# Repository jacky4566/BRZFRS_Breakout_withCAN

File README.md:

# BRZFRS_Breakout_withCAN

An inline ECU breakout board for the Subaru BRZ / Scion FR-S / Toyota 86 with a built-in CAN I/O module.

**CURRENTLY UNTESTED**

The board sits between your aftermarket ECU and the vehicle harness. All 135 ECU pins pass straight through. The board also taps the ECU's CAN bus and +5V supply to power a small STM32 module. That module reads extra analog and digital inputs, sends them on the CAN bus, and drives four low-side outputs on CAN command.

## Credits

The CAN I/O section is based on **[CANBoard](https://github.com/corygrant/CANBoard) by Cory Grant**, released under the MIT License (see [LICENSE.MD](LICENSE.MD)). This board adapts that design to the BRZ/FRS ECU connector form factor.

## Firmware

This board **requires Cory Grant's CANBoard firmware**. It does not work without it. Get the firmware, CAN message definitions and setup instructions from the original project:
https://github.com/corygrant/dingoFW

The MCU, CAN transceiver and I/O pin assignments come from the original CANBoard design. Refer to that project for the CAN message format and IDs.

### Programming

Flash the firmware over SWD with the **J1 Tag-Connect TC2030** footprint and an ST-Link (or another SWD probe) with a TC2030 cable.

## ECU connector taps

Every pin from J3 to J2 is wired 1:1. The CAN module connects to only these pins:

| ECU pin | Net | Use |
|--------:|-----|-----|
| A18 (18) | CAN_L | CAN bus low |
| A19 (19) | CAN_H | CAN bus high |
| D19 (120) | +5V | Powers the CAN module and the +5V pins on the headers |
| D29 (130) | GND | Signal ground |
| D03 (104), D04(105) | GNDPWR | Power ground for the output drivers |

The module runs from the ECU's +5V supply, so everything on the board and on the header +5V pins shares that supply. Keep the external load on the +5V pins small.

## Inputs

### Analog inputs: J7 (5 channels)

Each analog input has a 4.7k series resistor, a 10k resistor to ground and a 10nF filter capacitor before the STM32 ADC. The divider scales the input by about 0.68, so 3.3V at the ADC is about 4.85V at the pin.

Each input has a +5V pin next to it, so J7 can connect 3-wire sensors (signal, +5V, ground on J6) directly.

| J7 pin | Signal | MCU pin |
|-------:|--------|---------|
| 1 | +5V | |
| 2 | AI1 | PA0 |
| 3 | +5V | |
| 4 | AI2 | PA1 |
| 5 | +5V | |
| 6 | AI3 | PA2 |
| 7 | +5V | |
| 8 | AI4 | PA3 |
| 9 | +5V | |
| 10 | AI5 | PA4 |

### Digital inputs: J5 (8 channels)

Each digital input has a 10k series resistor to the MCU. There are no external pull-up or pull-down resistors. Input bias comes from the firmware's MCU pin configuration.

| J5 pin | Signal | MCU pin |
|-------:|--------|---------|
| 1 | DI1 | PA5 |
| 2 | DI2 | PA6 |
| 3 | DI3 | PA7 |
| 4 | DI4 | PB0 |
| 5 | DI5 | PB1 |
| 6 | DI6 | PA8 |
| 7 | DI7 | PA9 |
| 8 | DI8 | PA10 |

## Outputs

### Low-side outputs: J4 (4 channels)

The outputs use two NCV8402D dual low-side drivers. Each channel switches its pin to power ground (GNDPWR) and is rated for:

- 42V, 2A per channel
- Short-circuit protection
- Thermal shutdown with automatic restart
- Overvoltage protection
- Built-in clamp for inductive loads (relays, solenoids)

Connect the load between a positive supply and the DIGOUT pin. The supply can be the +5V pin beside each output (small 5V loads only) or switched 12V from the vehicle (relays, lamps, solenoids). The driver completes the circuit to ground when the output is on.

| J4 pin | Signal | MCU pin |
|-------:|--------|---------|
| 1 | DIGOUT1 | PA15 |
| 2 | +5V | |
| 3 | DIGOUT2 | PB3 |
| 4 | +5V | |
| 5 | DIGOUT3 | PB4 |
| 6 | +5V | |
| 7 | DIGOUT4 | PB5 |
| 8 | +5V | |

### Ground: J6

J6 pins 1 to 4 are all signal GND, for sensor and switch returns.

## CAN ID selection

Solder jumpers **JP1** (PB7) and **JP2** (PB6) select the module's CAN ID, as on the original CANBoard. Bridging a jumper (1) pulls its pin high through a 10k resistor.

| JP1 | JP2 | CAN ID |
|:---:|:---:|:------:|
| 0 | 0 | 0x640 |
| 1 | 0 | 0x650 |
| 0 | 1 | 0x660 |
| 1 | 1 | 0x670 |

See the [CANBoard firmware](https://github.com/corygrant/CANBoard) for the message layout at each ID.

## Repository contents

| File / folder | Description |
|---------------|-------------|
| `BRZ_Breakout_withCAN.kicad_pro` | KiCad project |
| `BRZ_Breakout_withCAN.kicad_sch` | Top-level schematic (ECU connectors and I/O headers) |
| `CANBoard.kicad_sch` | CAN module sub-sheet (MCU, CAN, power, I/O conditioning) |
| `BRZ_Breakout_withCAN.kicad_pcb` | PCB layout |
| `6376430-2/`, `Project.pretty/`, `*.kicad_sym` | Project symbols, footprints and 3D model for the ECU connector and NCV8402D |
| `bom/ibom.html` | Interactive BOM |

## License

MIT. See [LICENSE.MD](LICENSE.MD). The original CANBoard design is © 2023 Cory Grant.

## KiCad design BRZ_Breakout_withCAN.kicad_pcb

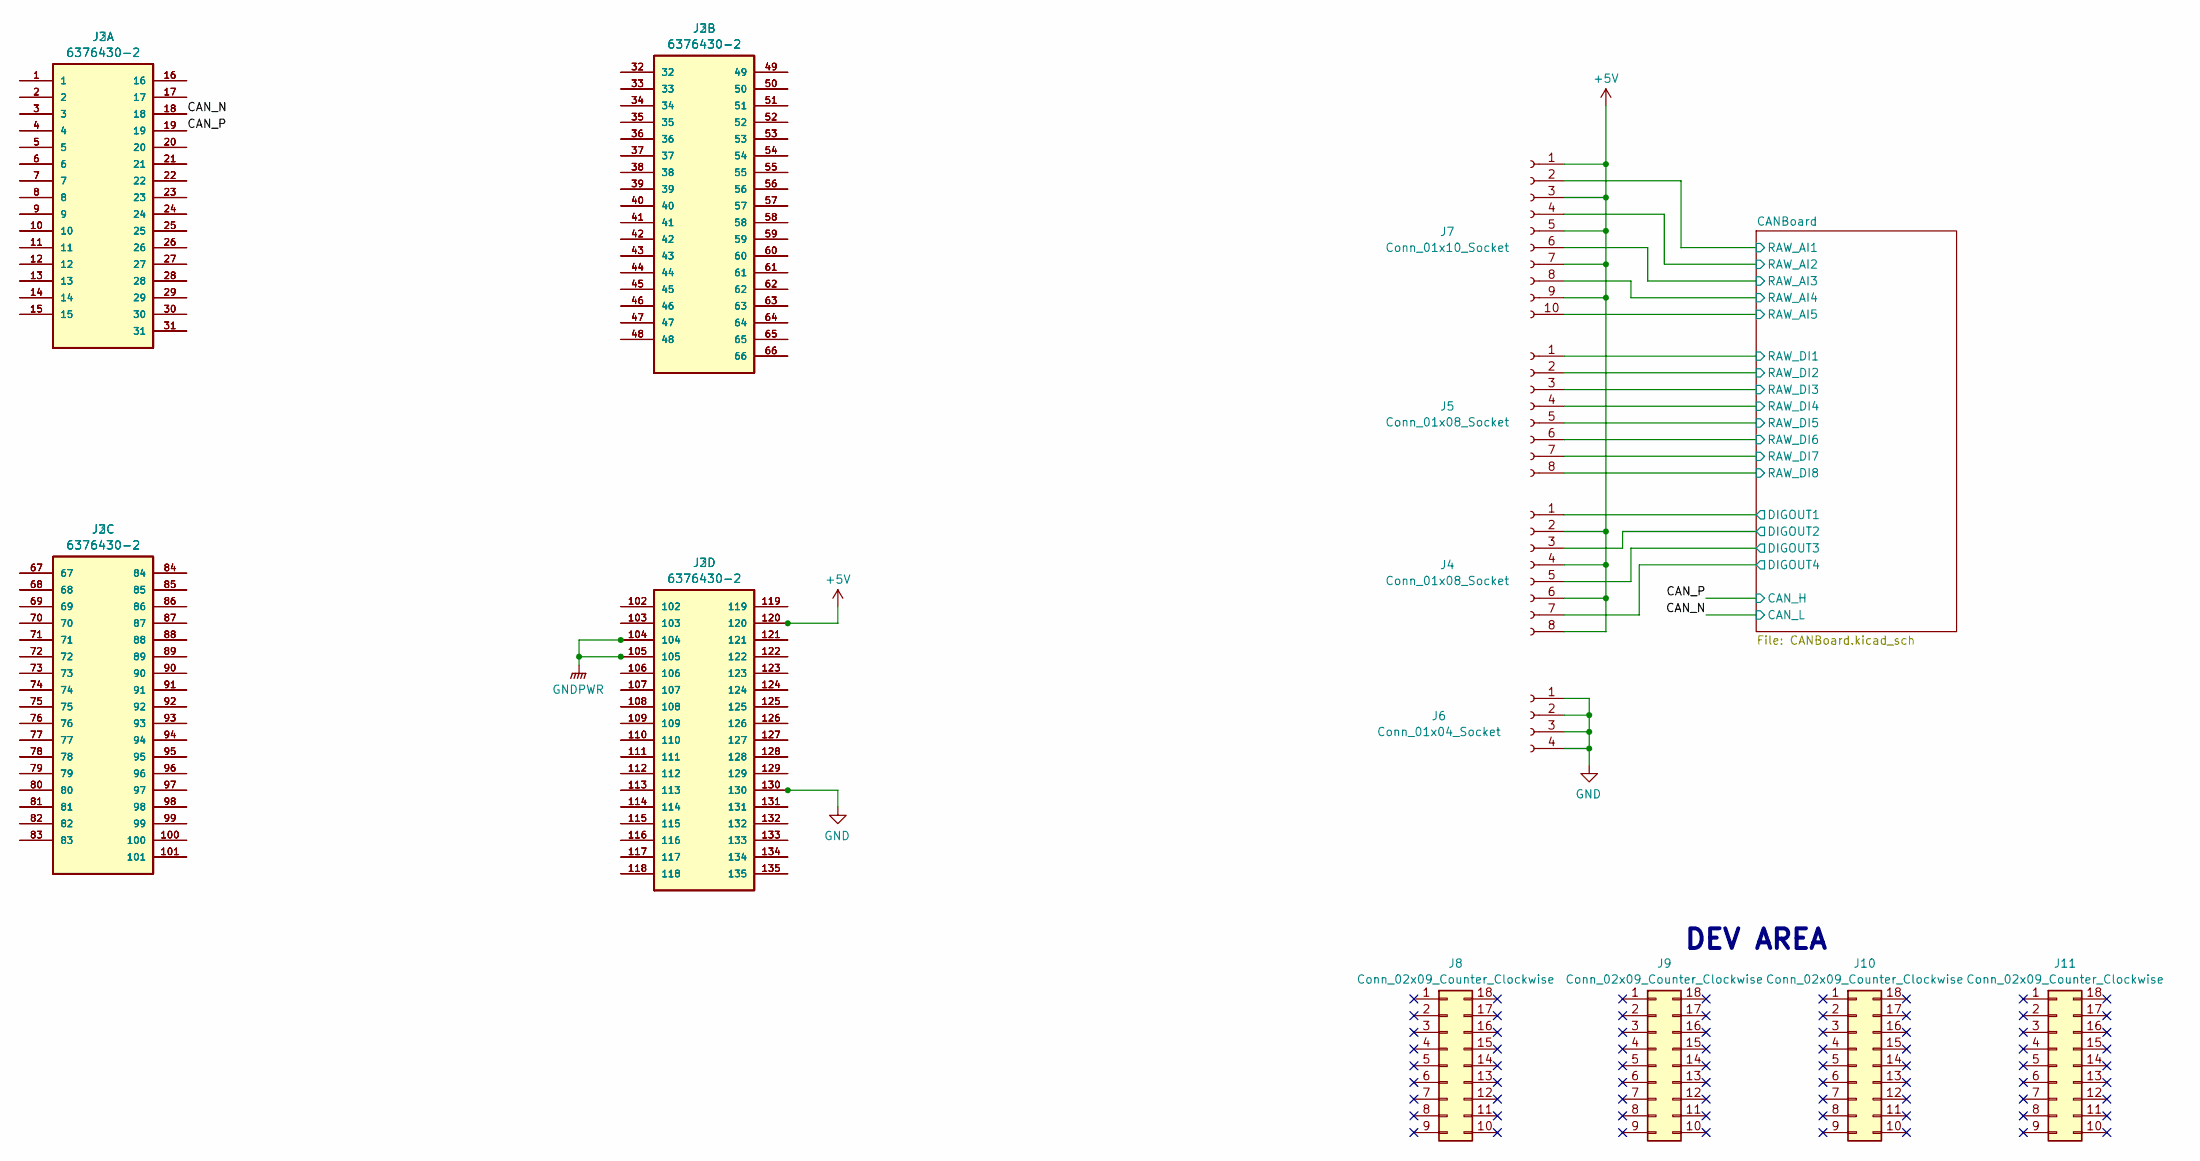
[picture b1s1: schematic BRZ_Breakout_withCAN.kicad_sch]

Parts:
J2, J3: 6376430-2; TE_6376430-2; MPN 6376430-2; Digi-Key_PN 17-6376430-2-ND
J4, J5: Conn_01x08_Socket; PinHeader_1x08_P2.54mm_Vertical
J6: Conn_01x04_Socket; PinHeader_1x04_P2.54mm_Vertical
J7: Conn_01x10_Socket; PinHeader_1x10_P2.54mm_Vertical
J8, J9, J10, J11: Conn_02x09_Counter_Clockwise; PinHeader_2x09_P2.54mm_Vertical

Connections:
+5V: J2.120, J3.120, J4.2, J4.4, J4.6, J4.8, J7.1, J7.3, J7.5, J7.7, J7.9; also elsewhere on the board
/CANBoard/DIGOUT1: J4.1; also elsewhere on the board
/CANBoard/DIGOUT2: J4.3; also elsewhere on the board
/CANBoard/DIGOUT3: J4.5; also elsewhere on the board
/CANBoard/DIGOUT4: J4.7; also elsewhere on the board
/CANBoard/RAW_AI1: J7.2; also elsewhere on the board
/CANBoard/RAW_AI2: J7.4; also elsewhere on the board
/CANBoard/RAW_AI3: J7.6; also elsewhere on the board
/CANBoard/RAW_AI4: J7.8; also elsewhere on the board
/CANBoard/RAW_AI5: J7.10; also elsewhere on the board
/CANBoard/RAW_DI1: J5.1; also elsewhere on the board
/CANBoard/RAW_DI2: J5.2; also elsewhere on the board
/CANBoard/RAW_DI3: J5.3; also elsewhere on the board
/CANBoard/RAW_DI4: J5.4; also elsewhere on the board
/CANBoard/RAW_DI5: J5.5; also elsewhere on the board
/CANBoard/RAW_DI6: J5.6; also elsewhere on the board
/CANBoard/RAW_DI7: J5.7; also elsewhere on the board
/CANBoard/RAW_DI8: J5.8; also elsewhere on the board
/CAN_N: J2.18, J3.18; also elsewhere on the board
/CAN_P: J2.19, J3.19; also elsewhere on the board
GND: J2.130, J3.130, J6.1, J6.2, J6.3, J6.4; also elsewhere on the board
GNDPWR: J2.104, J2.105, J3.104, J3.105; also elsewhere on the board
unnamed: J2.1, J3.1
unnamed: J2.2, J3.2
unnamed: J2.3, J3.3
unnamed: J2.4, J3.4
unnamed: J2.5, J3.5
unnamed: J2.6, J3.6
unnamed: J2.7, J3.7
unnamed: J2.8, J3.8
unnamed: J2.9, J3.9
unnamed: J2.10, J3.10
unnamed: J2.11, J3.11
unnamed: J2.12, J3.12
unnamed: J2.13, J3.13
unnamed: J2.14, J3.14
unnamed: J2.15, J3.15
unnamed: J2.16, J3.16
unnamed: J2.17, J3.17
unnamed: J2.20, J3.20
unnamed: J2.21, J3.21
unnamed: J2.22, J3.22
unnamed: J2.23, J3.23
unnamed: J2.24, J3.24
unnamed: J2.25, J3.25
unnamed: J2.26, J3.26
unnamed: J2.27, J3.27
unnamed: J2.28, J3.28
unnamed: J2.29, J3.29
unnamed: J2.30, J3.30
unnamed: J2.31, J3.31
unnamed: J2.32, J3.32
unnamed: J2.33, J3.33
unnamed: J2.34, J3.34
unnamed: J2.35, J3.35
unnamed: J2.36, J3.36
unnamed: J2.37, J3.37
unnamed: J2.38, J3.38
unnamed: J2.39, J3.39
unnamed: J2.40, J3.40
unnamed: J2.41, J3.41
unnamed: J2.42, J3.42
unnamed: J2.43, J3.43
unnamed: J2.44, J3.44
unnamed: J2.45, J3.45
unnamed: J2.46, J3.46
unnamed: J2.47, J3.47
unnamed: J2.48, J3.48
unnamed: J2.49, J3.49
unnamed: J2.50, J3.50
unnamed: J2.51, J3.51
unnamed: J2.52, J3.52
unnamed: J2.53, J3.53
unnamed: J2.54, J3.54
unnamed: J2.55, J3.55
unnamed: J2.56, J3.56
unnamed: J2.57, J3.57
unnamed: J2.58, J3.58
unnamed: J2.59, J3.59
unnamed: J2.60, J3.60
unnamed: J2.61, J3.61
unnamed: J2.62, J3.62
unnamed: J2.63, J3.63
unnamed: J2.64, J3.64
unnamed: J2.65, J3.65
unnamed: J2.66, J3.66
unnamed: J2.67, J3.67
unnamed: J2.68, J3.68
unnamed: J2.69, J3.69
unnamed: J2.70, J3.70
unnamed: J2.71, J3.71
unnamed: J2.72, J3.72
unnamed: J2.73, J3.73
unnamed: J2.74, J3.74
unnamed: J2.75, J3.75
unnamed: J2.76, J3.76
unnamed: J2.77, J3.77
unnamed: J2.78, J3.78
unnamed: J2.79, J3.79
unnamed: J2.80, J3.80
unnamed: J2.81, J3.81
unnamed: J2.82, J3.82
unnamed: J2.83, J3.83
unnamed: J2.84, J3.84
unnamed: J2.85, J3.85
unnamed: J2.86, J3.86
unnamed: J2.87, J3.87
unnamed: J2.88, J3.88
unnamed: J2.89, J3.89
unnamed: J2.90, J3.90
unnamed: J2.91, J3.91
unnamed: J2.92, J3.92
unnamed: J2.93, J3.93
unnamed: J2.94, J3.94
unnamed: J2.95, J3.95
unnamed: J2.96, J3.96
unnamed: J2.97, J3.97
unnamed: J2.98, J3.98
unnamed: J2.99, J3.99
unnamed: J2.100, J3.100
unnamed: J2.101, J3.101
unnamed: J2.102, J3.102
unnamed: J2.103, J3.103
unnamed: J2.106, J3.106
unnamed: J2.107, J3.107
unnamed: J2.108, J3.108
unnamed: J2.109, J3.109
unnamed: J2.110, J3.110
unnamed: J2.111, J3.111
unnamed: J2.112, J3.112
unnamed: J2.113, J3.113
unnamed: J2.114, J3.114
unnamed: J2.115, J3.115
unnamed: J2.116, J3.116
unnamed: J2.117, J3.117
unnamed: J2.118, J3.118
unnamed: J2.119, J3.119
unnamed: J2.121, J3.121
unnamed: J2.122, J3.122
unnamed: J2.123, J3.123
unnamed: J2.124, J3.124
unnamed: J2.125, J3.125
unnamed: J2.126, J3.126
unnamed: J2.127, J3.127
unnamed: J2.128, J3.128
unnamed: J2.129, J3.129
unnamed: J2.131, J3.131
unnamed: J2.132, J3.132
unnamed: J2.133, J3.133
unnamed: J2.134, J3.134
unnamed: J2.135, J3.135

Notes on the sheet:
DEV AREA

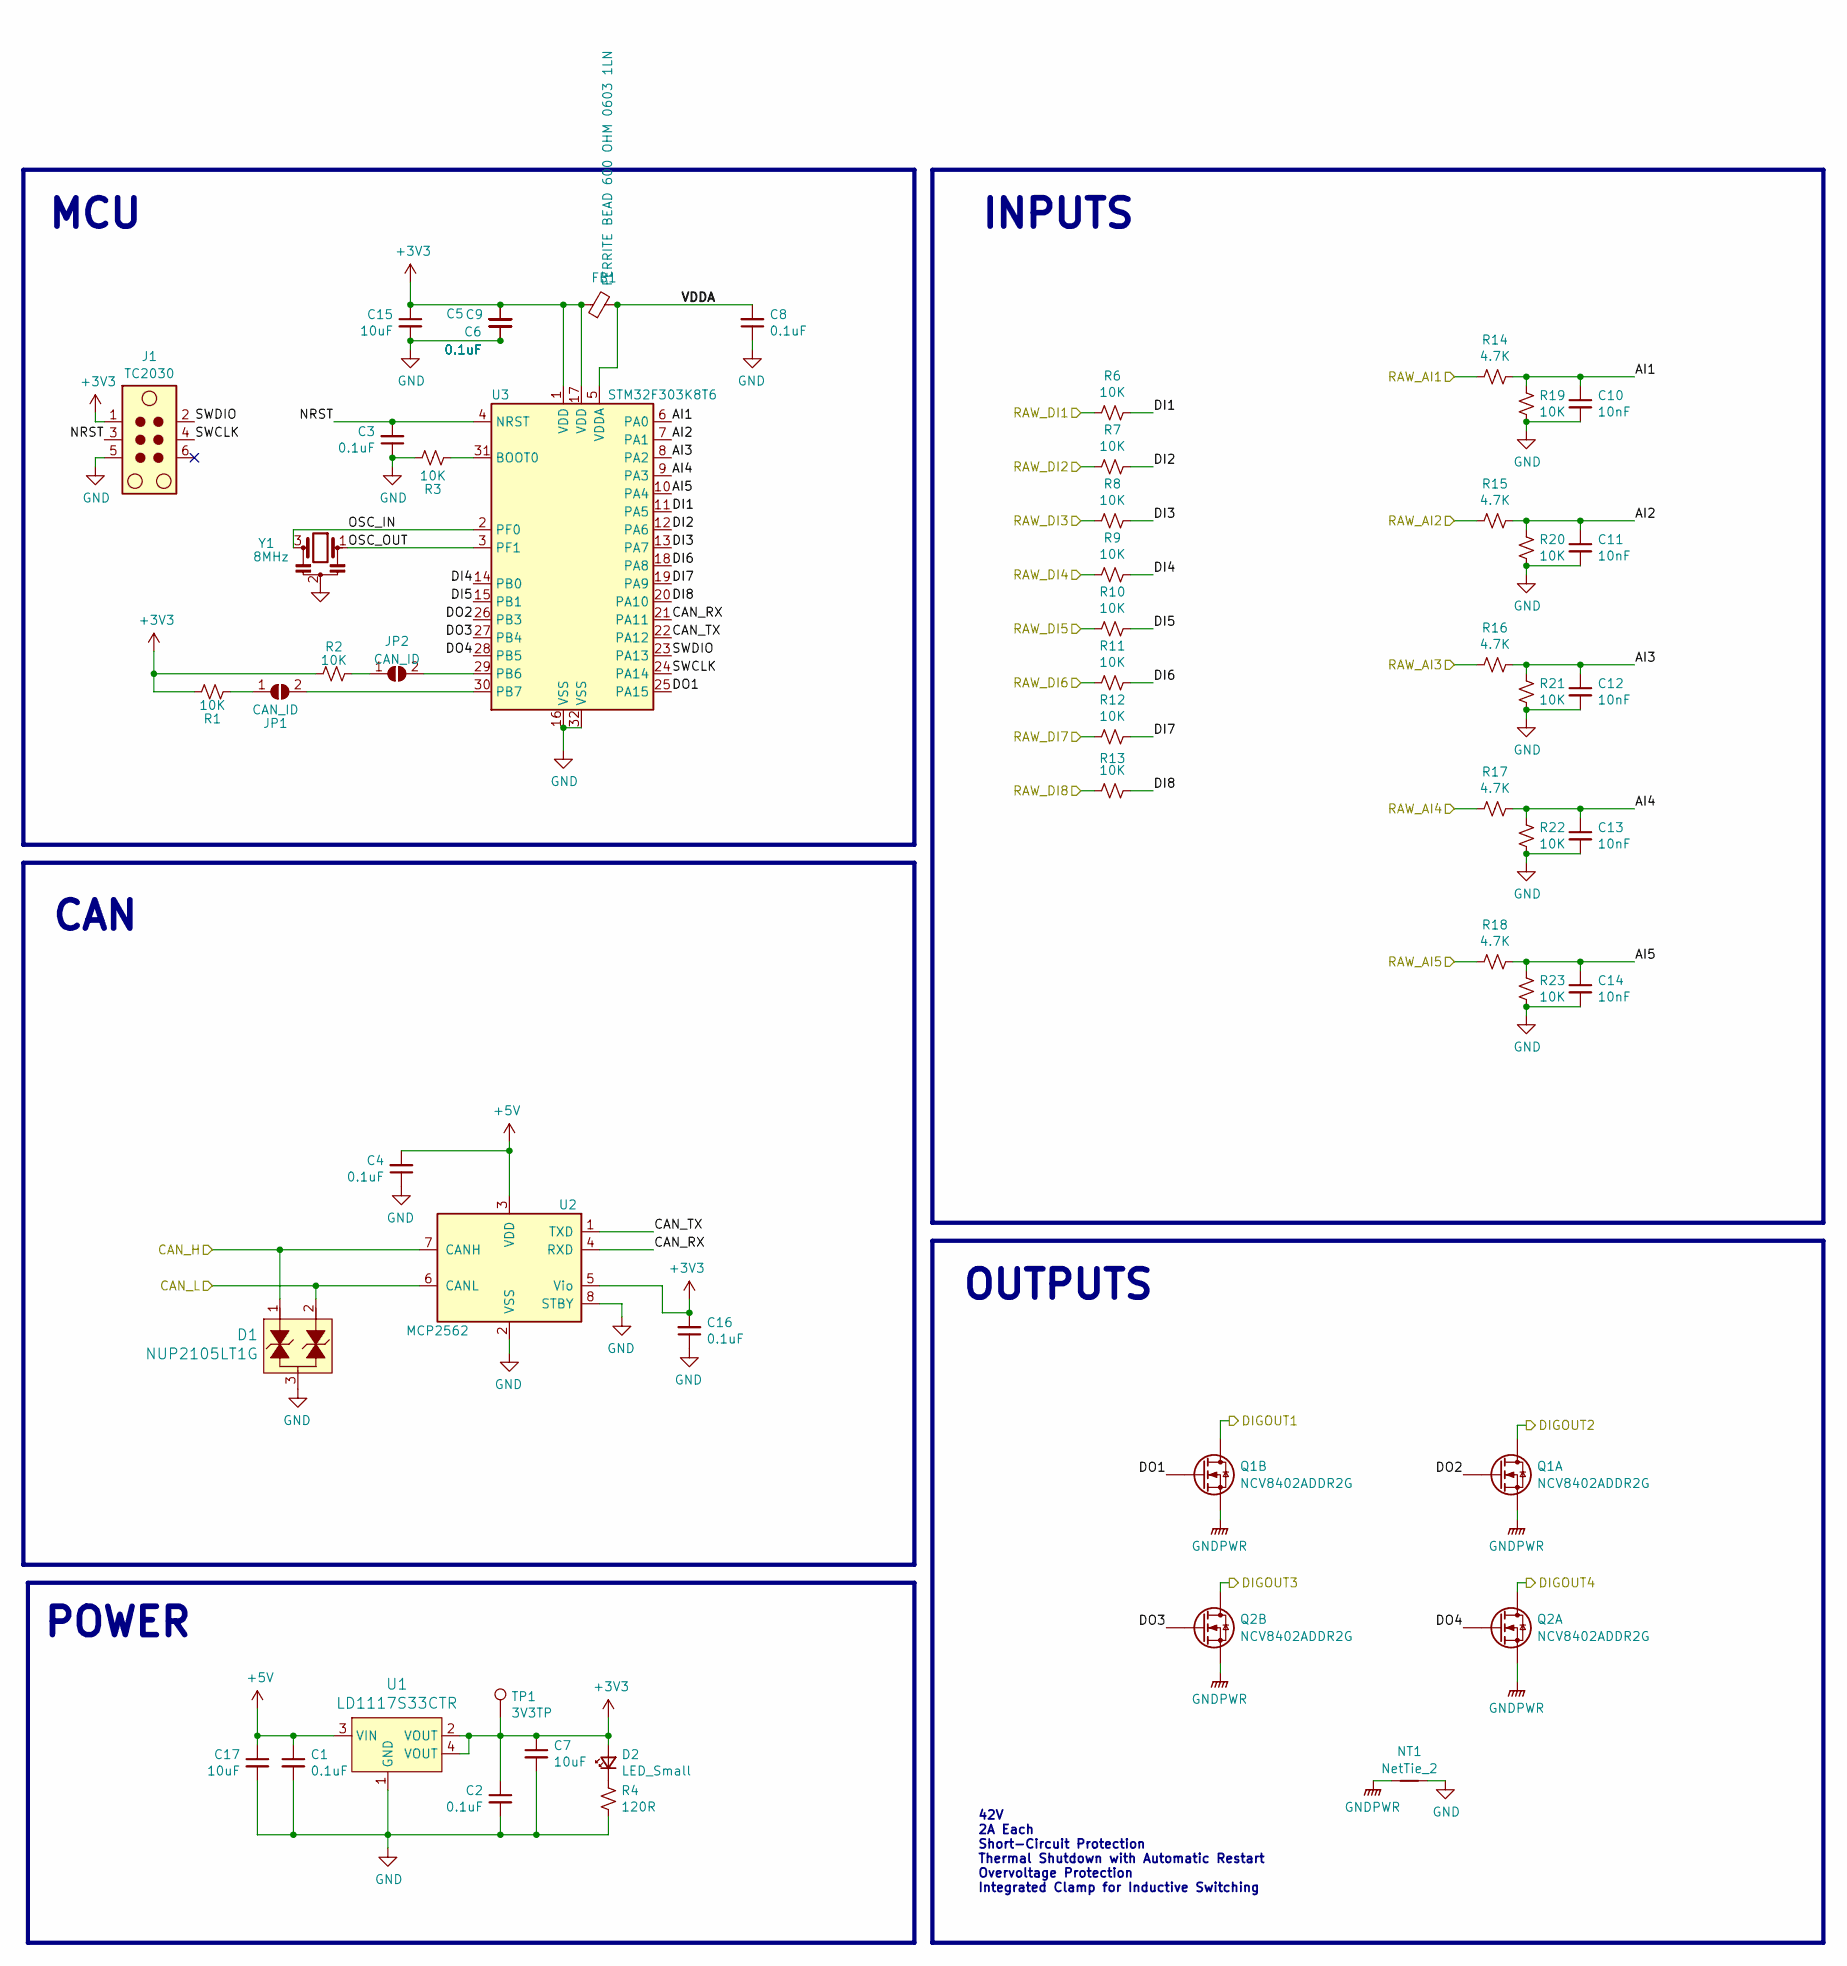
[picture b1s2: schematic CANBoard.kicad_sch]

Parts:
C1, C2, C3, C4, C5, C6, C8, C9, C16: 0.1uF; C_0603_1608Metric; MPN C0603C104K3RACTU; Digi-Key_PN 399-C0603C104K3RACTUCT-ND
C7, C15, C17: 10uF; C_0805_2012Metric; MPN GRM21BR61E106MA73L; Digi-Key_PN 490-10748-1-ND
C10, C11, C12, C13, C14: 10nF; C_0603_1608Metric; MPN C0603C103K5RACTU; Digi-Key_PN 399-C0603C103K5RACTUCT-ND
D1: NUP2105LT1G; SOT-23-3; MPN NUP2105LT1G; Digi-Key_PN NUP2105LT1GOSCT-ND
D2: LED_Small; LED_0805_2012Metric; MPN LY R976-PS-36-0-20-R18; Digi-Key_PN 475-2560-1-ND
FB1: FERRITE BEAD 600 OHM 0603 1LN; R_0603_1608Metric; MPN BLM18AG601SH1D; Digi-Key_PN 490-7811-1-ND
J1: TC2030; Tag-Connect_TC2030-IDC-NL_2x03_P1.27mm_Vertical
JP1, JP2: CAN_ID; SolderJumper-2_P1.3mm_Open_RoundedPad1.0x1.5mm
NT1: NetTie_2; NetTie-2_THT_Pad0.3mm
Q1, Q2: NCV8402ADDR2G; SOIC-8_3.9x4.9mm_P1.27mm; MPN NCV8402ADDR2G; Digi-Key_PN NCV8402ADDR2GOSCT-ND
R1, R2, R3, R6, R7, R8, R9, R10, R11, R12, R13, R19, R20, R21, R22, R23: 10K; R_0603_1608Metric; MPN CRCW060310K0FKEA; Digi-Key_PN 541-10.0KHCT-ND
R4: 120R; R_0603_1608Metric; MPN RC0603JR-07120RL; Digi-Key_PN 311-120GRCT-ND
R14, R15, R16, R17, R18: 4.7K; R_0603_1608Metric; MPN CRCW06034K70FKEA; Digi-Key_PN 541-4.70KHCT-ND
TP1: 3V3TP; TestPoint_Pad_D1.0mm
U1: LD1117S33CTR; SOT-223; MPN LD1117S33CTR; Digi-Key_PN 497-1241-1-ND
U2: MCP2562; SOIC-8_3.9x4.9mm_P1.27mm; MPN MCP2562-H/SN; Digi-Key_PN MCP2562-H/SN-ND
U3: STM32F303K8T6; LQFP-32_7x7mm_P0.8mm; MPN STM32F303K8T6; Digi-Key_PN 497-15828-ND
Y1: 8MHz; Resonator_SMD_Murata_CSTxExxV-3Pin_3.0x1.1mm; MPN 490-17959-1-ND; Digi-Key_PN 490-17959-1-ND

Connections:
+3V3: C2.1, C5.2, C6.2, C7.1, C9.2, C15.1, C16.2, D2.2 (A), FB1.1, J1.1, R1.2, R2.2, TP1.1 (1_1), U1.2 (VOUT), U1.4 (VOUT), U2.5 (Vio), U3.1 (VDD), U3.17 (VDD)
+5V: C1.1, C4.2, C17.1, U1.3 (VIN), U2.3 (VDD); also elsewhere on the board
/CANBoard/AI1: C10.1, R14.1, R19.2, U3.6 (PA0)
/CANBoard/AI2: C11.1, R15.1, R20.2, U3.7 (PA1)
/CANBoard/AI3: C12.1, R16.1, R21.2, U3.8 (PA2)
/CANBoard/AI4: C13.1, R17.1, R22.2, U3.9 (PA3)
/CANBoard/AI5: C14.1, R18.1, R23.2, U3.10 (PA4)
/CANBoard/CAN_RX: U2.4 (RXD), U3.21 (PA11)
/CANBoard/CAN_TX: U2.1 (TXD), U3.22 (PA12)
/CANBoard/DI1: R6.1, U3.11 (PA5)
/CANBoard/DI2: R7.1, U3.12 (PA6)
/CANBoard/DI3: R8.1, U3.13 (PA7)
/CANBoard/DI4: R9.1, U3.14 (PB0)
/CANBoard/DI5: R10.1, U3.15 (PB1)
/CANBoard/DI6: R11.1, U3.18 (PA8)
/CANBoard/DI7: R12.1, U3.19 (PA9)
/CANBoard/DI8: R13.1, U3.20 (PA10)
/CANBoard/DIGOUT1: Q1.5 (D), Q1.6 (D); also elsewhere on the board
/CANBoard/DIGOUT2: Q1.7 (D), Q1.8 (D); also elsewhere on the board
/CANBoard/DIGOUT3: Q2.5 (D), Q2.6 (D); also elsewhere on the board
/CANBoard/DIGOUT4: Q2.7 (D), Q2.8 (D); also elsewhere on the board
/CANBoard/DO1: Q1.4 (G), U3.25 (PA15)
/CANBoard/DO2: Q1.2 (G), U3.26 (PB3)
/CANBoard/DO3: Q2.4 (G), U3.27 (PB4)
/CANBoard/DO4: Q2.2 (G), U3.28 (PB5)
/CANBoard/NRST: C3.2, J1.3, U3.4 (NRST)
/CANBoard/OSC_IN: U3.2 (PF0), Y1.3
/CANBoard/OSC_OUT: U3.3 (PF1), Y1.1
/CANBoard/RAW_AI1: R14.2; also elsewhere on the board
/CANBoard/RAW_AI2: R15.2; also elsewhere on the board
/CANBoard/RAW_AI3: R16.2; also elsewhere on the board
/CANBoard/RAW_AI4: R17.2; also elsewhere on the board
/CANBoard/RAW_AI5: R18.2; also elsewhere on the board
/CANBoard/RAW_DI1: R6.2; also elsewhere on the board
/CANBoard/RAW_DI2: R7.2; also elsewhere on the board
/CANBoard/RAW_DI3: R8.2; also elsewhere on the board
/CANBoard/RAW_DI4: R9.2; also elsewhere on the board
/CANBoard/RAW_DI5: R10.2; also elsewhere on the board
/CANBoard/RAW_DI6: R11.2; also elsewhere on the board
/CANBoard/RAW_DI7: R12.2; also elsewhere on the board
/CANBoard/RAW_DI8: R13.2; also elsewhere on the board
/CANBoard/SWCLK: J1.4, U3.24 (PA14)
/CANBoard/SWDIO: J1.2, U3.23 (PA13)
/CANBoard/VDDA: C8.2, FB1.2, U3.5 (VDDA)
/CAN_N: D1.2, U2.6 (CANL); also elsewhere on the board
/CAN_P: D1.1, U2.7 (CANH); also elsewhere on the board
GND: C1.2, C2.2, C3.1, C4.1, C5.1, C6.1, C7.2, C8.1, C9.1, C10.2, C11.2, C12.2, C13.2, C14.2, C15.2, C16.1, C17.2, D1.3, J1.5, NT1.2, R3.2, R4.1, R19.1, R20.1, R21.1, R22.1, R23.1, U1.1 (GND), U2.2 (VSS), U2.8 (STBY), U3.16 (VSS), U3.32 (VSS), Y1.2; also elsewhere on the board
GNDPWR: NT1.1, Q1.1 (S), Q1.3 (S), Q2.1 (S), Q2.3 (S); also elsewhere on the board
unnamed: D2.1 (K), R4.2
unnamed: JP1.1 (A), R1.1
unnamed: JP1.2 (B), U3.30 (PB7)
unnamed: JP2.1 (A), R2.1
unnamed: JP2.2 (B), U3.29 (PB6)
unnamed: R3.1, U3.31 (BOOT0)

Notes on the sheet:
OUTPUTS
POWER
MCU
INPUTS
42V 2A Each Short−Circuit Protection Thermal Shutdown with Automatic Restart Overvoltage Protection Integrated Clamp for Inductive Switching
CAN

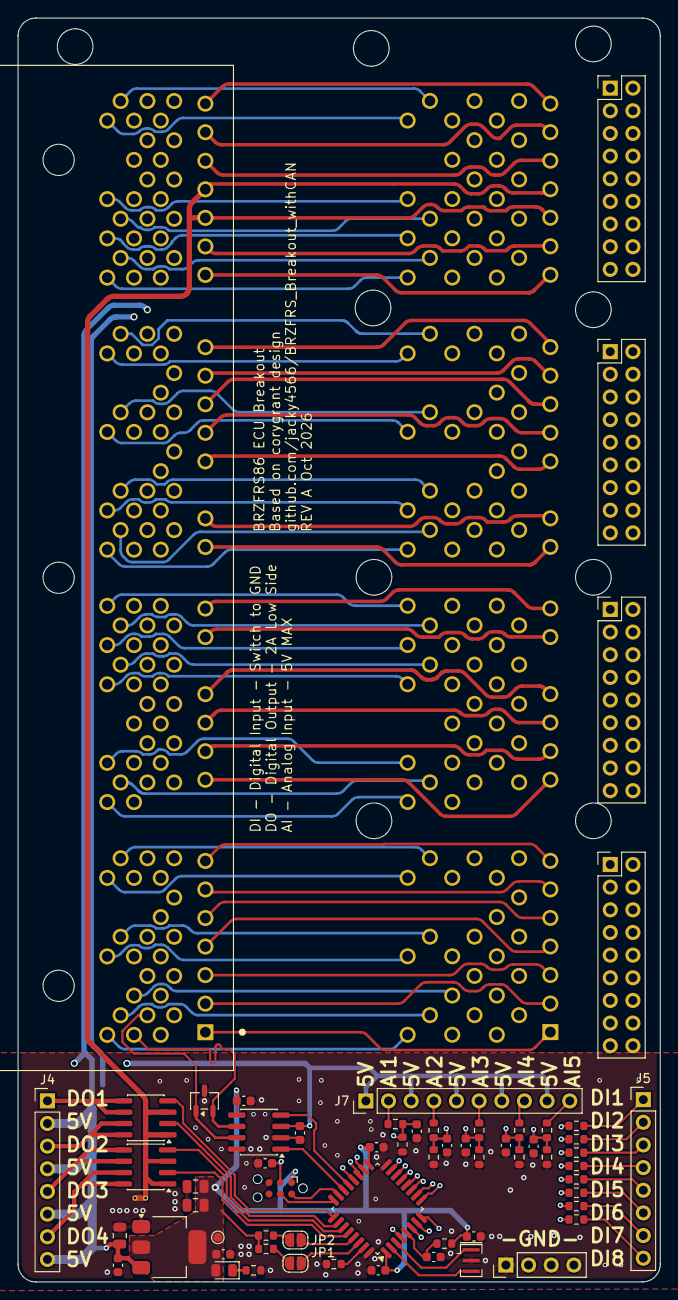
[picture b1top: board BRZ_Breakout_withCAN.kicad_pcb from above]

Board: 4 copper layers, 72.0 x 141.7 mm, 63 parts (0 on the bottom side), 183 nets.
